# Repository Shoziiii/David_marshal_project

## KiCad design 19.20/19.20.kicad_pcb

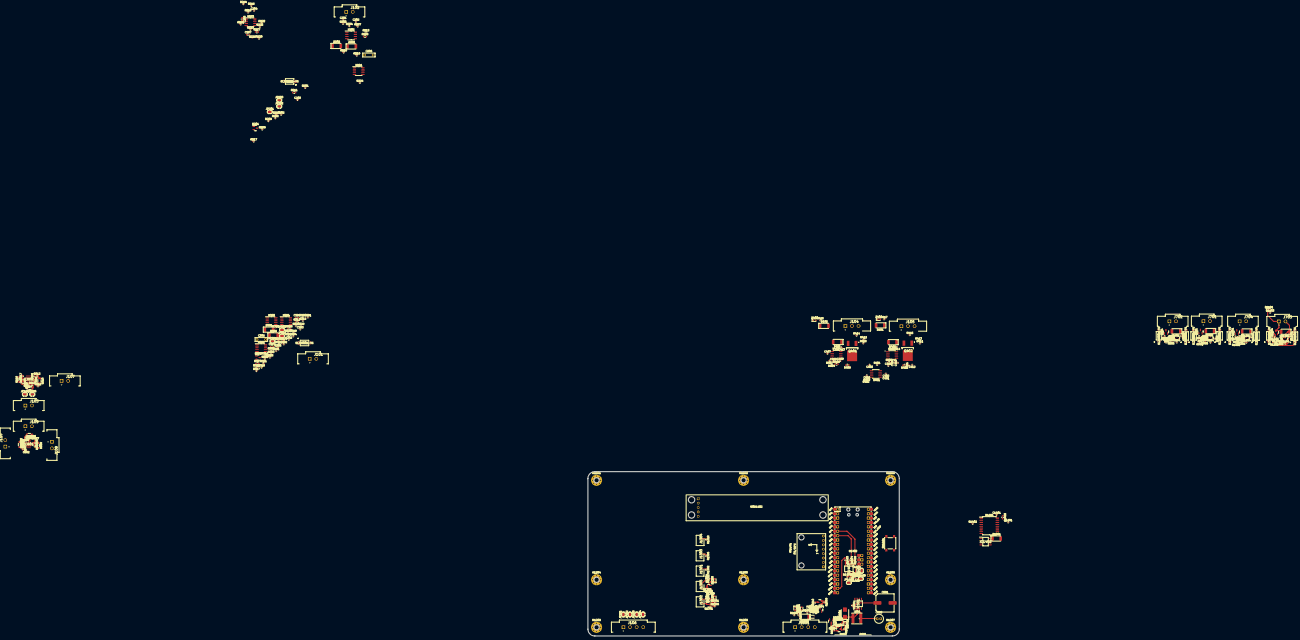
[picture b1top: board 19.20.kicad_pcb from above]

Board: 2 copper layers, 180.0 x 95.0 mm, 313 parts (0 on the bottom side), 193 nets.

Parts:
C201, C202, C301, C302, C413, C414: 1nf; C_0402_1005Metric
C203, C204, C303, C304, C402, C403, C404, C405, C406, C408, C410, C1404: 10nf; C_0402_1005Metric
C205, C207, C305, C307: 470pf; C_0603_1608Metric
C206, C306: 220nf; C_Rect_L7.0mm_W2.0mm_P5.00mm
C401, C407, C409, C411, C412, C601, C602, C603, C604, C605, C606, C607, C608: 100nf; C_0402_1005Metric
C501: 470uF; C_Elec_10x10.2
C502: 1uf; C_0402_1005Metric
C503: 180uF; C_Radial_D5.0mm_H11.0mm_P2.00mm
C1401, C1402: 100nF; C_0402_1005Metric
C1403: 10uf; C_0603_1608Metric
D101, D102, D201, D202, D301, D302, D401, D402, D802, D902, D1002, D1102, D1501, D1501#2, D1602: SM4007; D_MELF
D403, D404, D801, D901, D1001, D1101, D1301, D1302, D1502, D1601, D1604, D1605: LED RED; LED_0603_1608Metric
D501: D_Schottky; D_SMB
D1603: D_Schottky; D_SOD-323
H1201, H1202, H1203, H1204, H1205, H1206, H1207, H1208, H1209: MountingHole_Pad; MountingHole_3.2mm_M3_Pad_Via
IC501: XL1509-5.0E1; SOIC127P600X175-8N
IC601, IC602: INA3221AIRGVR; QFN65P400X400X100-17N-D
IC1401: MB85RC64VPNF-G-JNERE1; SOIC127P600X175-8N
J101, J102, J103, J107, J108, J109, J110, J701, J702, J703, J704: TBP02R1W-381-02BE; 15EDGVM-3.81-02P-14-00A(H)
J104, J105: TBP02R1W-381-03BE; 15EDGVM-3.81-03P-14-00A(H)
J106, J1601: TBP02R1W-381-04BE; CUI_TBP02R1W-381-04GR-UPDATE
J1301, J1302, J1303, J1304, J1305: B2B-PH-K-S_LF__SN_; SHDR2W50P0X200_1X2_590X450X600P
JP101, JP102, JP103, JP104, JP105, JP106, JP201, JP202, JP203, JP301, JP302, JP303, JP1402: SolderJumper_2_Open; SolderJumper-2_P1.3mm_Open_RoundedPad1.0x1.5mm
JP1401, JP1403: SolderJumper_2_Bridged; SolderJumper-2_P1.3mm_Bridged_RoundedPad1.0x1.5mm
L501: 68uH; L_6.0x6.0_4.5
MOD1401: GY-521
MOD1402: 8DIG7SEGDISPLAY; 8DIG7SEDDISPLAY
Q201, Q301, Q802, Q902, Q1002, Q1102, Q1502, Q1504: AO3401A; SOT-23
Q401, Q402: NJVMJD122T4G-VF01; NJVMJD122T4GVF01
Q801, Q901, Q1001, Q1101: AO3400A; SOT-23
Q1301, Q1302, Q1501, Q1503: MMBT5551L; SOT-23
R201, R212, R301, R312, R416, R417: 200R; R_0402_1005Metric
R202, R203, R205, R207, R209, R221, R224, R302, R303, R305, R307, R309, R321, R324, R410, R411, R414, R415, R803, R805, R806, R903, R905, R906, R1003, R1005, R1006, R1103, R1105, R1106, R1301, R1304, R1307, R1309, R1401, R1403, R1404, R1405, R1408, R1409, R1501, R1504, R1505, R1602: 10k; R_0402_1005Metric
R204, R214, R215, R304, R314, R315, R401: 220k; R_0402_1005Metric
R208, R308, R403, R1306, R1507: 1.2k; R_0402_1005Metric
R211, R220, R311, R320, R801, R901, R1001, R1101: 150R; R_0603_1608Metric
R213, R222, R223, R313, R322, R323: 100k; R_0402_1005Metric
R216, R316: 1M; R_0402_1005Metric
R217, R317: 6.8k; R_0402_1005Metric
R218, R225, R318, R325, R1406, R1407, R1506, R1601, R1603: 22k; R_0402_1005Metric
R219, R319: 10M; R_0402_1005Metric
R226, R326: 22k; R_01005_0402Metric
R227, R327: 100R; R_0603_1608Metric
R228, R328: 47R; R_0402_1005Metric
R402, R404: 4.7k; R_0402_1005Metric
R405, R406, R408, R409: 43k; R_0603_1608Metric
R407: 470k; R_0402_1005Metric
R412, R413, R802, R804, R902, R904, R1002, R1004, R1102, R1104, R1302, R1303, R1305, R1308, R1310, R1311, R1402, R1502, R1503, R1508, R1509, R1510: 2.4k; R_0402_1005Metric
R601, R605, R609, R610, R614, R618: 20R; R_1206_3216Metric
R602, R603, R604, R606, R607, R608, R611, R612, R613, R615, R616, R617: 10R; R_0402_1005Metric
R807, R907, R1007, R1107: 1.5k; R_0402_1005Metric
R1410: 120R; R_0402_1005Metric
SW1401: SW_MEC_5E; SW_SPST_PTS645
U201, U301, U801, U802, U901, U902, U1001, U1002, U1101, U1102: EL3H7BTA-VG
U202, U204, U302, U304: MCP6002-xSN; SOIC-8_3.9x4.9mm_P1.27mm
U203, U303: LM358; SOIC-8_3.9x4.9mm_P1.27mm
U401, U402, U403: NE555DR; SOIC127P599X175-8N
U1401: PCF8574; SOIC-16W_7.5x10.3mm_P1.27mm
U1402: Pico; RPi_Pico_SMD_TH
U1403: MAX3485; SOIC127P600X175-8N 2

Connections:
3V3: C602.2, C606.1, IC601.4 (VS), IC601.16 (VPU), IC602.4 (VS), IC602.5 (A0), IC602.16 (VPU)
3V3_PI: C1401.2, C1402.1, C1403.2, C1404.2, IC1401.8 (VDD), MOD1401.1 (VCC), Q1504.2 (S), R1401.1, R1402.2, R1403.1, R1404.1, R1405.1, R1406.2, R1408.2, R1409.2, R1509.1, U1401.16 (VDD), U1402.36 (3V3), U1403.8 (VCC)
5V0: C411.2, C412.2, C503.1, IC501.3 (FEEDBACK), L501.2, MOD1402.5 (VCC), Q401.4, Q402.4, R214.1, R314.1, R408.1, R409.1, U202.8 (V+), U204.8 (V+), U302.8 (V+), U304.8 (V+), U402.8 (VCC), U403.8 (VCC), U801.4 (C), U901.4 (C), U1001.4 (C), U1101.4 (C), U1402.39 (VSYS)
/555 Coil/C1: C414.1, D402.1 (K), J105.2, Q402.3, R415.1, R417.2
/555 Coil/CO: C413.1, D401.1 (K), J104.2, Q401.3, R414.1, R416.2
/Current Sensor 01/420MA_N01A+: J103.1, JP105.2 (B), R616.2, R618.1
/Current Sensor 01/420MA_N01B-: R228.2, R617.2, R618.2
/Current Sensor 01/420MA_N02A+: J103.2, JP106.2 (B), R613.2, R614.1
/Current Sensor 01/420MA_N02B-: R328.2, R614.2, R615.2
/Current Sensor 01/420MA_N03A+: J107.1, R610.1, R612.2
/Current Sensor 01/420MA_N03B-: J106.1, JP101.1 (A), R610.2, R611.2
/Current Sensor 01/420MA_N04A+: J108.1, R607.2, R609.1
/Current Sensor 01/420MA_N04B-: J106.2, JP102.1 (A), R608.2, R609.2
/Current Sensor 01/420MA_N05A+: J109.1, R604.2, R605.2
/Current Sensor 01/420MA_N05B-: J106.3, JP103.1 (A), R605.1, R606.2
/Current Sensor 01/420MA_N06A+: J110.1, R601.2, R603.2
/Current Sensor 01/420MA_N06B-: J106.4, JP104.1 (A), R601.1, R602.2
/Current Sensor 01/SCL: IC601.6 (SCL), IC602.6 (SCL), IC1401.6 (SCL), JP1403.2 (B), MOD1401.3 (SCL), U1401.14 (SCL), U1402.12 (GPIO9)
/Current Sensor 01/SDA: IC601.7 (SDA), IC602.7 (SDA), IC1401.5 (SDA), JP1401.2 (B), MOD1401.4 (SDA), U1401.15 (SDA), U1402.11 (GPIO8)
/GP06: R201.1, U1402.9 (GPIO6)
/GP07: R301.1, U1402.10 (GPIO7)
/MCU/Ex_P0: R805.2, R807.1, U1401.4 (P0)
/MCU/Ex_P1: R905.2, R907.1, U1401.5 (P1)
/MCU/Ex_P2: R1005.2, R1007.1, U1401.6 (P2)
/MCU/Ex_P3: R1105.2, R1107.1, U1401.7 (P3)
/MCU/Ex_P4: R801.1, U1401.9 (P4)
/MCU/Ex_P5: R901.1, U1401.10 (P5)
/MCU/Ex_P6: R1001.1, U1401.11 (P6)
/MCU/Ex_P7: R1101.1, U1401.12 (P7)
/MCU/GP04: R1403.2, U1402.6 (GPIO4), U1403.4 (DI)
/MCU/GP05: R1405.2, U1402.7 (GPIO5), U1403.1 (RO)
/MCU/GP14: R1404.2, U1402.19 (GPIO14), U1403.2 (~RE), U1403.3 (DE)
/MCU/GP15: R1501.1, R1502.2, U1402.20 (GPIO15)
/MCU/GP26: R1301.2, R1303.2, U1402.31 (GPIO26_ADC0)
/MCU/GP27: R1307.2, R1308.2, U1402.32 (GPIO27_ADC1)
/MCU/GP28: Q1504.3 (D), R1510.2, U1402.34 (GPIO28_ADC2)
/MCU/PICORUN: SW1401.1, U1402.30 (RUN)
/SNS01/BUF: R315.1, U304.6 (-), U304.7
/SNS01/RST: C306.2, Q301.2 (S), R319.1, R320.2, U304.3 (+)
/SNS01/SNSX: C301.1, J101.2
/SNS2/BUF: R215.1, U204.6 (-), U204.7
/SNS2/RST: C206.2, Q201.2 (S), R219.1, R220.2, U204.3 (+)
/SNS2/SNSX: C201.1, J102.2
/Switched outputs/Switched 01/SWITCHED NEG: D801.1 (K), D802.2 (A), J702.1, Q801.3 (D)
/Switched outputs/Switched 01/SWITCHED POS: D802.1 (K), J702.2, Q802.3 (D), R803.2, R805.1
/Switched outputs/Switched 2/SWITCHED NEG: D901.1 (K), D902.2 (A), J701.1, Q901.3 (D)
/Switched outputs/Switched 2/SWITCHED POS: D902.1 (K), J701.2, Q902.3 (D), R903.2, R905.1
/Switched outputs/Switched 3/SWITCHED NEG: D1001.1 (K), D1002.2 (A), J704.1, Q1001.3 (D)
/Switched outputs/Switched 3/SWITCHED POS: D1002.1 (K), J704.2, Q1002.3 (D), R1003.2, R1005.1
/Switched outputs/Switched 4/SWITCHED NEG: D1101.1 (K), D1102.2 (A), J703.1, Q1101.3 (D)
/Switched outputs/Switched 4/SWITCHED POS: D1102.1 (K), J703.2, Q1102.3 (D), R1103.2, R1105.1
GND: C202.1, C203.1, C204.1, C206.1, C302.1, C303.1, C304.1, C306.1, C401.1, C403.1, C404.1, C405.2, C406.2, C407.1, C408.1, C409.1, C410.1, C411.1, C412.1, C413.2, C414.2, C501.2, C502.1, C503.2, C602.1, C606.2, C1401.1, C1402.2, C1403.1, C1404.1, D101.2 (A), D102.2 (A), D401.2 (A), D402.2 (A), D403.1 (K), D404.1 (K), D501.2 (A), D1502.1 (K), D1601.1 (K), D1602.2 (A), D1603.2 (A), D1604.1 (K), D1605.1 (K), H1201.1, H1202.1, H1203.1, H1204.1, H1205.1, H1206.1, H1207.1, H1208.1, H1209.1, IC501.5 (GND_1), IC501.6 (GND_2), IC501.7 (GND_3), IC501.8 (GND_4), IC601.3 (GND_1), IC601.5 (A0), IC602.3 (GND_1), IC1401.4 (VSS), J104.3, J105.3, J1301.2, J1303.2, J1304.2, J1601.4, JP101.2 (B), JP102.2 (B), JP103.2 (B), JP104.2 (B), JP105.1 (A), JP106.1 (A), MOD1401.2 (GND), MOD1402.4 (GND), Q801.2 (S), Q901.2 (S), Q1001.2 (S), Q1101.2 (S), Q1301.2 (E), Q1302.2 (E), Q1501.2 (E), Q1503.2 (E), R204.1, R205.1, R209.1, R212.2, R217.1, R219.2, R222.1, R304.1, R305.1, R309.1, R312.2, R317.1, R319.2, R322.1, R401.2, R403.2, R405.2, R406.2, R407.2, R410.2, R411.2, R414.2, R415.2, R807.2, R907.2, R1007.2, R1107.2, R1301.1, R1307.1, R1407.1, R1501.2, R1507.1, R1510.1, U201.2 (K), U202.4 (V-), U203.4 (V-), U204.4 (V-), U301.2 (K), U302.4 (V-), U303.4 (V-), U304.4 (V-), U401.1 (GND), U402.1 (GND), U403.1 (GND), U801.2 (K), U802.2 (K), U802.3 (E), U901.2 (K), U902.2 (K), U902.3 (E), U1001.2 (K), U1002.2 (K), U1002.3 (E), U1101.2 (K), U1102.2 (K), U1102.3 (E), U1401.1 (A0), U1401.3 (A2), U1401.8 (VSS), U1402.3 (GND), U1402.8 (GND), U1402.13 (GND), U1402.18 (GND), U1402.23 (GND), U1402.28 (GND), U1402.33 (AGND), U1402.38 (GND), U1403.5 (GND)
unnamed: C201.2, R203.2
unnamed: C202.2, R207.1
unnamed: C203.2, Q201.3 (D), R212.1
unnamed: C204.2, R215.2, R216.1, U203.3 (+)
unnamed: C205.1, R225.1, R227.1, U203.1
unnamed: C205.2, R217.2, R221.1, U203.2 (-)
unnamed: C207.1, R223.2, R226.1, U203.6 (-)
unnamed: C207.2, R221.2, R223.1, U203.7
unnamed: C301.2, R303.2
unnamed: C302.2, R307.1
unnamed: C303.2, Q301.3 (D), R312.1
unnamed: C304.2, R315.2, R316.1, U303.3 (+)
unnamed: C305.1, R325.1, R327.1, U303.1
unnamed: C305.2, R317.2, R321.1, U303.2 (-)
unnamed: C307.1, R323.2, R326.1, U303.6 (-)
unnamed: C307.2, R321.2, R323.1, U303.7
unnamed: C401.2, C402.1, R402.1, R403.1, U401.4 (RESET), U401.8 (VCC)
unnamed: C402.2, R401.1, U401.2 (TRIG), U401.6 (THRES)
unnamed: C403.2, U401.5 (CONT)
unnamed: C404.2, U401.7 (DISCH)
unnamed: C405.1, R404.2, R407.1, U402.4 (RESET)
unnamed: C406.1, R406.1, U401.3 (OUT), U403.4 (RESET)
unnamed: C407.2, U402.2 (TRIG), U402.6 (THRES)
unnamed: C408.2, U402.5 (CONT)
unnamed: C409.2, U403.2 (TRIG), U403.6 (THRES)
unnamed: C410.2, U403.5 (CONT)
unnamed: C601.1, IC601.2 (IN+3), R603.1
unnamed: C601.2, IC601.1 (IN-3), R602.1
unnamed: C603.1, IC601.15 (IN+2), R604.1
unnamed: C603.2, IC601.14 (IN-2), R606.1
unnamed: C604.1, IC601.12 (IN+1), R607.1
unnamed: C604.2, IC601.11 (IN-1), R608.1
unnamed: C605.1, IC602.2 (IN+3), R612.1
unnamed: C605.2, IC602.1 (IN-3), R611.1
unnamed: C607.1, IC602.15 (IN+2), R613.1
unnamed: C607.2, IC602.14 (IN-2), R615.1
unnamed: C608.1, IC602.12 (IN+1), R616.1
unnamed: C608.2, IC602.11 (IN-1), R617.1
unnamed: D201.1 (K), D202.2 (A), R218.1
unnamed: D201.2 (A), U202.7
unnamed: D202.1 (K), R220.1, U202.6 (-)
unnamed: D301.1 (K), D302.2 (A), R318.1
unnamed: D301.2 (A), U302.7
unnamed: D302.1 (K), R320.1, U302.6 (-)
unnamed: D403.2 (A), R416.1
unnamed: D404.2 (A), R417.1
unnamed: D501.1 (K), IC501.2 (OUTPUT), L501.1
unnamed: D801.2 (A), R803.1
unnamed: D901.2 (A), R903.1
unnamed: D1001.2 (A), R1003.1
unnamed: D1101.2 (A), R1103.1
unnamed: D1301.1 (K), J1302.2, Q1301.3 (C)
unnamed: D1301.2 (A), R1304.1
unnamed: D1302.1 (K), J1305.2, Q1302.3 (C)
unnamed: D1302.2 (A), R1309.1
unnamed: D1501.2 (A), D1501#2.2 (A), Q1502.3 (D), R1505.2
unnamed: D1502.2 (A), R1505.1
unnamed: D1601.2 (A), R1601.2
unnamed: D1604.2 (A), R1602.1
unnamed: D1605.2 (A), R1603.2
unnamed: J1301.1, R1302.1
unnamed: J1302.1, R1305.2
unnamed: J1303.1, R1306.1
unnamed: J1304.1, R1310.1
unnamed: J1305.1, R1311.2
unnamed: JP201.2 (B), JP203.2 (B), R208.2
unnamed: JP203.1 (A), U201.3 (E)
unnamed: JP301.2 (B), JP303.2 (B), R308.2
unnamed: JP303.1 (A), U301.3 (E)
unnamed: JP1401.1 (A), R1408.1
unnamed: JP1402.2 (B), R1410.2
unnamed: JP1403.1 (A), R1409.1
unnamed: Q201.1 (G), R211.2
unnamed: Q301.1 (G), R311.2
unnamed: Q401.1, R412.1
unnamed: Q402.1, R413.1
unnamed: Q801.1 (G), R802.1
unnamed: Q802.1 (G), R804.1, R806.2
unnamed: Q901.1 (G), R902.1
unnamed: Q902.1 (G), R904.1, R906.2
unnamed: Q1001.1 (G), R1002.1
unnamed: Q1002.1 (G), R1004.1, R1006.2
unnamed: Q1101.1 (G), R1102.1
unnamed: Q1102.1 (G), R1104.1, R1106.2
unnamed: Q1301.1 (B), R1303.1
unnamed: Q1302.1 (B), R1308.1
unnamed: Q1501.1 (B), R1502.1
unnamed: Q1501.3 (C), R1504.2
unnamed: Q1502.1 (G), R1503.2, R1504.1
unnamed: Q1503.1 (B), R1508.1
unnamed: Q1503.3 (C), Q1504.1 (G), R1509.2
unnamed: R201.2, U201.1 (A)
unnamed: R203.1, R204.2, U202.3 (+)
unnamed: R207.2, R213.1, U202.2 (-)
unnamed: R208.1, R209.2, R211.1
unnamed: R213.2, U202.1, U202.5 (+)
unnamed: R214.2, R216.2
unnamed: R218.2, R224.1, U204.1, U204.2 (-)
unnamed: R222.2, R225.2, U203.5 (+)
unnamed: R224.2, U204.5 (+)
unnamed: R226.2, R227.2, R228.1
unnamed: R301.2, U301.1 (A)
unnamed: R303.1, R304.2, U302.3 (+)
unnamed: R307.2, R313.1, U302.2 (-)
unnamed: R308.1, R309.2, R311.1
unnamed: R313.2, U302.1, U302.5 (+)
unnamed: R314.2, R316.2
unnamed: R318.2, R324.1, U304.1, U304.2 (-)
unnamed: R322.2, R325.2, U303.5 (+)
unnamed: R324.2, U304.5 (+)
unnamed: R326.2, R327.2, R328.1
unnamed: R408.2, U402.7 (DISCH)
unnamed: R409.2, U403.7 (DISCH)
unnamed: R410.1, R412.2, U402.3 (OUT)
unnamed: R411.1, R413.2, U403.3 (OUT)
unnamed: R801.2, U801.1 (A), U802.1 (A)
unnamed: R802.2, U801.3 (E)
unnamed: R806.1, U802.4 (C)
unnamed: R901.2, U901.1 (A), U902.1 (A)
unnamed: R902.2, U901.3 (E)
unnamed: R906.1, U902.4 (C)
unnamed: R1001.2, U1001.1 (A), U1002.1 (A)
unnamed: R1002.2, U1001.3 (E)
unnamed: R1006.1, U1002.4 (C)
unnamed: R1101.2, U1101.1 (A), U1102.1 (A)
unnamed: R1102.2, U1101.3 (E)
unnamed: R1106.1, U1102.4 (C)
unnamed: R1401.2, U1401.13 (~INT)
unnamed: R1402.1, U1401.2 (A1)
unnamed: R1506.2, R1507.2, R1508.2
unnamed: JP202.1 (A), R202.2, R205.2, U201.4 (C)
unnamed: JP302.1 (A), R302.2, R305.2, U301.4 (C)
P0-0: C501.1, C502.2, IC501.1 (VIN), J107.2, J108.2, J109.2, J110.2, J1601.1, Q802.2 (S), Q902.2 (S), Q1002.2 (S), Q1102.2 (S), Q1502.2 (S), R804.2, R904.2, R1004.2, R1104.2, R1302.2, R1304.2, R1305.1, R1309.2, R1311.1, R1503.1, R1603.1, U203.8 (V+), U303.8 (V+)
P0-1: D101.1 (K), D102.1 (K), J104.1, J105.1, J1601.2, JP201.1 (A), JP301.1 (A), R1306.2, R1602.2
P0-2: D1501.1 (K), D1501#2.1 (K), D1602.1 (K), D1603.1 (K), J1601.3, R202.1, R302.1, R1310.2, R1506.1, R1601.1
PO-2: R402.2, R404.1, R405.1
RS485_A: R1406.1, R1410.1, U1403.7 (B)
RS485_B: JP1402.1 (A), R1407.2, U1403.6 (A)
SPI1_CSN: MOD1402.2 (CS), U1402.17 (GPIO13)
SPI1_SCK: MOD1402.1 (CLK), U1402.14 (GPIO10)
SPI1_TX: MOD1402.3 (DIN), U1402.15 (GPIO11)

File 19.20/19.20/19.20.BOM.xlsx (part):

REG | Item | Qty | Reference(s) | Value | LibPart | Footprint | Datasheet | ARROW_ELECTRONICS-PURCHASE-URL | AVAILABILITY | Arrow Part Number | Arrow Price/Stock | DESCRIPTION | DIGIKEY-PURCHASE-URL | Description | Height | LCSC
x | 19 | 1 | J101 | TBP02R1W-381-02BE | :TBP02R1W-381-02BE_6 | Footprints:CUI_TBP02R1W-381-02GR | https://datasheet.lcsc.com/lcsc/2004011035_DEGSON-15EDGVM-3-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 |  |  |  |  |  |  |  |  | C507015
x | 21 | 1 | J104 | TBP02R1W-381-03BE | :TBP02R1W-381-03BE_1 | Footprints:CUI_TBP02R1W-381-03GR |  |  |  |  |  |  |  |  |  | C528717
x | 59 | 2 | U203, U303 | LM358 | Amplifier_Operational:LM358 | Footprints:SOIC-8_3.9x4.9mm_P1.27mm | http://www.ti.com/lit/ds/symlink/lm2904-n.pdf |  |  |  |  |  |  |  |  | C7950
x | 58 | 4 | U202, U204, U302, U304 | MCP6002-xSN | Amplifier_Operational:MCP6002-xSN | Footprints:SOIC-8_3.9x4.9mm_P1.27mm | http://ww1.microchip.com/downloads/en/DeviceDoc/21733j.pdf |  |  |  |  |  |  |  |  | C7377
 | 2 | 12 | C203, C204, C303, C304, C402, C403, C404, C405, C406, C408, C410, C1404 | 10nf | Device:C | Footprints:C_0402_1005Metric | ~ |  |  |  |  |  |  |  |  | C15195
 | 1 | 6 | C201, C202, C301, C302, C413, C414 | 1nf | Device:C | Footprints:C_0402_1005Metric | ~ |  |  |  |  |  |  |  |  | C1523
 | 3 | 4 | C205, C207, C305, C307 | 470pf | Device:C | Footprints:C_0603_1608Metric | ~ |  |  |  |  |  |  |  |  | C1620
 | 5 | 13 | C401, C407, C409, C411, C412, C601, C602, C603, C604, C605, C606, C607, C608 | 100nf | Device:C | Footprints:C_0402_1005Metric | ~ |  |  |  |  |  |  |  |  | C307331
 | 9 | 2 | C1401, C1402 | 100nF | Device:C | Footprints:C_0402_1005Metric | ~ |  |  |  |  |  |  |  |  | C307331
 | 7 | 1 | C502 | 1uf | Device:C | Footprints:C_0402_1005Metric | https://datasheet.lcsc.com/lcsc/1811091611_Samsung-Electro-M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 |  |  |  |  |  |  |  |  | C307413
 | 4 | 2 | C206, C306 | 220nf | Device:C | Footprints:C_Rect_L7.0mm_W2.0mm_P5.00mm | ~ |  |  |  |  |  |  |  |  | C393118
 | 10 | 1 | C1403 | 10uf | Device:C | Footprints:C_0603_1608Metric | https://datasheet.lcsc.com/lcsc/1811091611_Samsung-Electro-M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 |  |  |  |  |  |  |  |  | C92487
x | 6 | 1 | C501 | 470uF | Device:C_Polarized_Small | Footprints:C_Elec_10x10.2 | ~ |  |  |  |  |  |  |  |  | C131125
x | 8 | 1 | C503 | 180uF | Device:C_Polarized_Small | Footprints:C_Radial_D5.0mm_H11.0mm_P2.00mm | https://datasheet.lcsc.com/lcsc/1912111437_Ymin-LKMB1101C181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 |  |  |  |  |  |  |  |  | C442570
x | 14 | 1 | D1603 | D_Schottky | Device:D_Schottky | Footprints:D_SOD-323 | https://datasheet.lcsc.com/lcsc/1811141223_Nexperia-BAT54C-2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 |  |  |  |  |  |  |  |  | C37704
x | 13 | 1 | D501 | D_Schottky | Device:D_Schottky | Footprints:D_SMB | ~ |  |  |  |  |  |  |  |  | C47124
x | 27 | 1 | L501 | 68uH | Device:L | Footprints:L_6.0x6.0_4.5 | ~ |  |  |  |  |  |  |  |  | C53663
x | 12 | 12 | D403, D404, D801, D901, D1001, D1101, D1301, D1302, D1502, D1601, D1604, D1605 | LED RED | Device:LED | Footprints:LED_0603_1608Metric | https://datasheet.lcsc.com/lcsc/1810231112_Hubei-KENTO-Elec-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 |  |  |  |  |  |  |  |  | C2286
x | 32 | 4 | Q801, Q901, Q1001, Q1101 | AO3400A | Device:Q_NMOS_GSD | Footprints:SOT-23 | https://datasheet.lcsc.com/lcsc/1811081213_Alpha---Omega-Sem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 |  |  |  |  |  |  |  |  | C20917
 | 45 | 2 | R227, R327 | 100R | Device:R | Footprints:R_0603_1608Metric | ~ |  |  |  |  |  |  |  |  | C22775
 | 38 | 4 | R211, R220, R311, R320 | 150R | Device:R | Footprints:R_0603_1608Metric | ~ |  |  |  |  |  |  |  |  | C22808
 | 52 | 12 | R602, R603, R604, R606, R607, R608, R611, R612, R613, R615, R616, R617 | 10R | Device:R | Footprints:R_0402_1005Metric | ~ |  |  |  |  |  |  |  |  | C25077
 | 55 | 1 | R1410 | 120R | Device:R | Footprints:R_0402_1005Metric | ~ |  |  |  |  |  |  |  |  | C25079
 | 34 | 10 | R201, R212, R301, R312, R416, R417, R808, R908, R1008, R1108 | 200R | Device:R | Footprints:R_0402_1005Metric | https://datasheet.lcsc.com/lcsc/2110252230_UNI-ROYAL-Uniroya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 |  |  |  |  |  |  |  |  | C25087
 | 53 | 4 | R801, R901, R1001, R1101 | 470R | Device:R | Footprints:R_0402_1005Metric | ~ |  |  |  |  |  |  |  |  | C25117
 | 46 | 2 | R228, R328 | 47R | Device:R | Footprints:R_0402_1005Metric | ~ |  |  |  |  |  |  |  |  | C25118
 | 39 | 6 | R213, R222, R223, R313, R322, R323 | 100k | Device:R | Footprints:R_0402_1005Metric | ~ |  |  |  |  |  |  |  |  | C25741
 | 35 | 48 | R202, R203, R205, R206, R207, R209, R210, R221, R224, R302, R303, R305, R306, R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 | 10k | Device:R | Footprints:R_0402_1005Metric | ~ |  |  |  |  |  |  |  |  | C25744
 | 36 | 7 | R204, R214, R215, R304, R314, R315, R401 | 220k | Device:R | Footprints:R_0402_1005Metric | ~ |  |  |  |  |  |  |  |  | C25744
 | 44 | 2 | R226, R326 | 22k | Device:R | Footprints:R_01005_0402Metric | ~ |  |  |  |  |  |  |  |  | C25744
 | 42 | 9 | R218, R225, R318, R325, R1406, R1407, R1506, R1601, R1603 | 22k | Device:R | Footprints:R_0402_1005Metric | ~ |  |  |  |  |  |  |  |  | C25768
 | 49 | 1 | R407 | 470k | Device:R | Footprints:R_0402_1005Metric | ~ |  |  |  |  |  |  |  |  | C25790
 | 48 | 4 | R405, R406, R408, R409 | 43k | Device:R | Footprints:R_0603_1608Metric | ~ |  |  |  |  |  |  |  |  | C25804
 | 37 | 5 | R208, R308, R403, R1306, R1507 | 1.2k | Device:R | Footprints:R_0402_1005Metric | ~ |  |  |  |  |  |  |  |  | C25862
 | 54 | 4 | R807, R907, R1007, R1107 | 1.5k | Device:R | Footprints:R_0402_1005Metric | ~ |  |  |  |  |  |  |  |  | C25867
 | 50 | 22 | R412, R413, R802, R804, R902, R904, R1002, R1004, R1102, R1104, R1302, R1303, R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 | 2.4k | Device:R | Footprints:R_0402_1005Metric | https://datasheet.lcsc.com/lcsc/2110260030_UNI-ROYAL-Uniroya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 |  |  |  |  |  |  |  |  | C25882
 | 47 | 2 | R402, R404 | 4.7k | Device:R | Footprints:R_0402_1005Metric | ~ |  |  |  |  |  |  |  |  | C25900
 | 41 | 2 | R217, R317 | 6.8k | Device:R | Footprints:R_0402_1005Metric | ~ |  |  |  |  |  |  |  |  | C25917
 | 43 | 2 | R219, R319 | 10M | Device:R | Footprints:R_0402_1005Metric | ~ |  |  |  |  |  |  |  |  | C26082
 | 40 | 2 | R216, R316 | 1M | Device:R | Footprints:R_0402_1005Metric | ~ |  |  |  |  |  |  |  |  | C26083
 | 51 | 6 | R601, R605, R609, R610, R614, R618 | 20R | Device:R | Footprints:R_1206_3216Metric | ~ |  |  |  |  |  |  |  |  | C319757
x | 11 | 14 | D101, D102, D201, D202, D301, D302, D401, D402, D802, D902, D1002, D1102, D1501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 | SM4007 | Diode:SM4007 | Footprints:D_SOD-123F | http://cdn-reichelt.de/documents/datenblatt/A400/SMD1N400%23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 |  |  |  |  |  |  |  |  | C64898
x | 61 | 1 | U1401 | PCF8574 | Interface_Expansion:PCF8574 | Footprints:SOIC-16W_7.5x10.3mm_P1.27mm | https://www.nxp.com/docs/en/data-sheet/PCF8574_PCF8574A.pdf |  |  |  |  |  |  |  |  | C7605
x | 63 | 1 | U1403 | MAX3485 | Interface_UART:MAX3485 | Footprints:SOIC127P600X175-8N 2 | https://datasheets.maximintegrated.com/en/ds/MAX3483-MAX3491.pdf |  |  |  |  |  |  |  |  | C9943
x | 57 | 10 | U201, U301, U801, U802, U901, U902, U1001, U1002, U1101, U1102 | PC817 | Isolator:PC817 | Footprints:SOIC-4 4.6 X 6.5 _2.54 | http://www.soselectronic.cz/a_info/resource/d/pc817.pdf |  |  |  |  |  |  |  |  | C169111
 | 26 | 2 | JP1401, JP1403 | SolderJumper_2_Bridged | Jumper:SolderJumper_2_Bridged |  | ~
 | 25 | 11 | JP101, JP102, JP103, JP104, JP201, JP202, JP203, JP301, JP302, JP303, JP1402 | SolderJumper_2_Open | Jumper:SolderJumper_2_Open | Footprints:SolderJumper-2_P1.3mm_Open_RoundedPad1.0x1.5mm | ~
 | 15 | 9 | H1201, H1202, H1203, H1204, H1205, H1206, H1207, H1208, H1209 | MountingHole_Pad | Mechanical:MountingHole_Pad | Footprints:MountingHole_3.2mm_M3_Pad_Via | ~
 | 29 | 1 | MOD1402 | 8DIG7SEGDISPLAY | PCB_Library:8DIG7SEGDISPLAY | Footprints:8DIG7SEDDISPLAY | https://cdn-shop.adafruit.com/datasheets/MAX7219.pdf
x | 24 | 5 | J1301, J1302, J1303, J1304, J1305 | B2B-PH-SM4-TBT_LF__SN_ | PCB_Library:B2B-PH-SM4-TBT_LF__SN_ | Footprints:B2BPHSM4TBTLFSN | http://www.jst-mfg.com/product/pdf/eng/ePH.pdf |  |  | B2B-PH-SM4-TBT(LF)(SN) | https://www.arrow.com/en/products/b2b-ph-sm4-tbt-lf-sn/jst-m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 |  |  | CONN HEADER SMD 2POS 2MM | 6.6 | C173752
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
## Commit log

2022-06-06 Added new files
2022-06-06 Checking
2022-06-06 Updated the schematic

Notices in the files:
parts and their libraries:
Copyright 2021 Accelerated Designs. All rights reserved.
